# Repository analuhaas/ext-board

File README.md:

# External measurement board

As part of the CARROTS project, we develop a MMC prototype using the OwnTech Suite. WP1 develops the hardware prototype. WP2 and WP3 use this prototype to develop and test decentralized control and communication.

To do classic MMC closed-loop control, it is necessary to have external measurement boards to measure the DC voltage $u_{dc}$, DC current $i_{dc}$, phase voltage $v_{p}$, phase current $i_{p}$ and arm currents $i_{u,l}$. Also, the MMC start-up require a resistance + relay system on the DC/AC sides for current limitation. Figure 1 shows the necessary measurements outside of the modules and the position of the correspondent external measurement boards.

# Board structure

The external measurement board general structure is represented in Figure 2. It is composed of a power and a digital part separated by a galvanic isolation. The power part circuit is shown in Figure 3. It is composed of a power relay, 2 voltage measurements and 1 current measurement. The connectors A-B side is called "upstream" and connectors C-D side is called "downstream". The digital part is composed of a microcontroller (SPIN) that reads the measurements and sends to the controller and other modules via RS485 communication.

# KiCad schematic development

## Power circuit

The power part of the external measurement board is composed of a solid state relay that connects upstream side to downstream side, connectors that connects to the converter circuit and voltage/current sensors.

**Questions left for discussion:**

- **For now I have kept the backplane structure as used for the modules for compatibility, but we also evoked the possibility of using banana connectors.**
- **Added a 1 MΩ resistor R282 between PUPGND and PDOWNGND, so the two grounds are at the same voltage before the relay closes.**

## Voltage and current sensors

The measurement solution is the same used in the new module board. The voltage raw measurement is acquired using a voltage divisor. The current raw measurement is acquired by an IC current sensor.

Then, both raw measurements are amplified and sent to the digital part of the board using a galvanic isolated amplifier.

Finally, the voltage and current measurements are treated by an analog front-end that is able to change the sensor gain, offset and resolution according to the application.

**Questions left for discussion:**

- **Which value to use in R249 and R254?**

## SPIN

The SPIN is the microcontroller part of the board. The SPIN from OwnVerter solution is kept but some changes on the pinout were necessary:

- Adapt the pins to the measurements we implemented (Vup, Vdown, IAB)

- Add a command for the relay

## Communication

The RS485 communication is used to communicate the boards measurement with the controller/other modules of the converter. It can also receive commands to open/close the switch.

CAN and analog communications are also included in the schematic since they are a part of the base OwnTech solution.

The communication RJ45 terminals pins order are modified from latest board versions (TWIST V1.4.3 and OWNVERTER V1.1) to be correspondent to the pins used in the WP4 redesigned modules.

**Questions left for discussion:**

- **A adaptation to communicate with previous board versions is then necessary?**
- **Adaptation to communicate with 3 different buses**

## Auxiliary circuits supply

We adapted the auxiliary circuits supply feed generation of the microinverter project <https://github.com/owntech-foundation/micro-inverter>. The auxiliary circuits are fed by 5 VDGND, 5 VPUPGND and 5VPDOWNGND derived by the 12 VDGND input. The 12 VDGND input must be supplied by an external DC source.

The TPS7420 linear voltage regulator is used on the output of all +5V feeds to filter signal noises and keep the output on the target 5 V voltage.

**Questions left for discussion:**

- **Need to update the notes on consumption of the the supply circuits.**

## Datasheets referencing

There still some elements that have different datasheets reference (in PEBB too) compared to their LCSC number. Also there are some datasheets that are not specified:

**Datasheet referenced does not correspond to the LCSC part:**

**Datasheet not specified:**

- Connectors: U809 (PwrBlade 51722-10602-0020)

Passive elements, mounting holes (H1 to H6), solder jumpers (JP406, JP410, JP417) and the eurocard rails (N101) do not need a datasheet.

## BOM referencing

- No LCSC number: R249 and R254 (5.6 k 0805), and U809 (its value is also ~).

# KiCad Layout

## General structure

The board PCB has a structure divided in two parts, digital (upper) and power (lower), separated by a isolation area of 8 mm as defined by the IEC 60664 standard.

The board dimensions are reduced to 100mmx100mm compared to the usual 100mmx160mm of the OwnVerter/Twist boards.

The board keeps the same railtracks and mount holes for mechanical fixation as the OwnVerter/Twist boards. The 4 lower mount holes positions where adapted to position a safety bow around the board power part, avoiding user direct contact.

In the following sections, certain components positioning details are defined.

## Relay

The relay and its activation circuit on digital-side are shown in Figure 18. The relay is placed across the isolation area.

The activation circuit is placed in a certain distance from the relay to allow the placement of the security box.

##  Auxiliary supply for PUPGND/PDOWNGND referenced components

The CMT8830U power transformer is used to isolate the 5 VDGND to 5 VPUPGND/5 VPDOWNGND. The CMP6503S isolated power transformer driver is used to drive the transformer. In its datasheet, its recommended positioning with respect to the transformer is as shown in Figure 19.

The TPS7420 linear voltage regulator is used on the output of all +5V feeds to filter signal noises and keep the output on the target 5 V voltage. In its datasheet, its recommended positioning with respect to the input and output capacitors is as shown in Figure 20.

With the guidance of these datasheets indications the placement for the PDOWNGND referenced side was implemented as shown in Figure 21. The driver circuit is distanced from the transformer to allow the placement of the security box.

The placement for the PUPGND part is similar, but the buck circuit was moved to under the switch due to lack of space in the layout power part.

## Auxiliary supply for DGND referenced components

To pass from 12 VDGND to 5 VDGND voltage, the TPS562202 buck converter is used. The positioning of the commutation cell with respect to the other buck components are done as suggested in the datasheet as shown in Figure 23.

The TPS7420 linear voltage regulator is used on the output of all +5V feeds to filter signal noises and keep the output on the target 5 V voltage. In its datasheet, its recommended positioning with respect to the input and output capacitors is as shown in Figure 20.

The 5VDGND generation layout is shown in Figure 25.

## Voltage measurement circuit

The AMC1311x isolated amplifier is used to isolate the raw measurement of the power side from the digital measurement that is used by the MCU. In its datasheet, its recommended positioning with respect to the voltage divisor, input RC filter and decoupling capacitors is shown in Figure 26.

With the guidance of these datasheets indications the placement for both PUPGND/PDOWNGND referenced side was implemented as shown in Figure 27. The resistors where placed to avoid letting different potentials close to each other.

The analog-front end gets this digital output from the amplifier and adapts it according to user set gain, offset and resolution. The placement of the analog front-end for the 2 voltage measurements and current measurement was kept near the top part of the board as in the module boards developed by WP4, shown in Figure 28.

## Current measurement circuit

The ACS724 isolated current sensor is used to acquire the raw current measurement passing from A to B connectors of the board. There is no recommended layout position in its datasheet, so the components where placed as close as possible to the pins. To have a smaller current path, the current sensor was placed the closest as possible to the relay I+ pin and VDOWN connector.

Similarly to the voltage measurement, the AMC1311x isolated amplifier is used to isolate the raw measurement of the power side from the digital measurement that is used by the MCU. In its datasheet, its recommended positioning with respect to the voltage divisor, input RC filter and decoupling capacitors is shown in Figure 26.

With the guidance of these datasheets indications, the placement of the current measurement circuit was implemented as shown in Figure 29.

# Wiring development

## +12VDGND, +5VDGND, +5VPUPGND and +5VPDOWNGND feeding

The components feeding in the digital part was concentrated in the In2 layer. The widths of each one were estimated using the KiCad width calculator considering $\Delta T = 10 °C$ and H = 35 µm.

### +12VDGND width

To the left side, the +12VDGND input supplies the MOSFET that drives the relay and the realy. The relay consumption of the 12 V input is of 67 mA according to the microinverter project notes. Given this, we estimated:

| Current (A) | Conductor length (mm) | Calculated width (mm) |
|:-------------------------------:|:---------------------:|:---------------------:|
|0.067|72|0.0188|

To give a safety marge for the relay consumption and to use TWIST/SPIN usual values for feeding traces width, we used 0.25 mm width for the conductor feeding the relay + relay MOSFET.

To the right side, the +12VDGND input supplies all the other digital side components, since it feeds the +5VDGND and +5VDCLEARGND and the power side comonents, since the +5VDGND feeds the +5VPUPGND and +5VPDOWNGND. We make a list of its main components consumption in current:

| Component | Current (mA) |
|:----------|:-----------:|
| **+5VPUPGND loads** (fed through U802 + TR801 + U804) | |
| U205 AMC1311 isolated amplifier high-side supply (IDD1) | 9.7 |
| R38 transformer pre-load (5 V / 4.7 kΩ) | 1.1 |
| *Subtotal +5VPUPGND* | *10.8* |
| **+5VPDOWNGND loads** (fed through U803 + TR802 + U805) | |
| U207 AMC1311 isolated amplifier high-side supply (IDD1) | 9.7 |
| U211 AMC1311 isolated amplifier high-side supply (IDD1) | 9.7 |
| U801 ACS724 current sensor (ICC) | 15 |
| R58 transformer pre-load (5 V / 4.7 kΩ) | 1.1 |
| R280 + R281 divider on ACS724 output | 0.2 |
| *Subtotal +5VPDOWNGND* | *35.7* |
| **+5VDCLEANGND loads** (fed through U806) | |
| U205 AMC1311 isolated amplifier low-side supply (IDD2) | 8.1 |
| U207 AMC1311 isolated amplifier low-side supply (IDD2) | 8.1 |
| U211 AMC1311 isolated amplifier low-side supply (IDD2) | 8.1 |
| AFE801, AFE802, AFE807 analog front-ends (estimate, all three) | 100 |
| *Subtotal +5VDCLEANGND* | *124.3* |
| **+5VDGND loads** (fed by U14 buck) | |
| U401 SPIN (estimate) | 100 |
| U402 CA-IF1051S CAN transceiver | 80 |
| U405 CA-IF4850HS RS485 transceiver (driving 54 Ω) | 70 |
| U406 MCP6487 dual op-amp (2 × 0.72 mA) | 1.4 |
| R431 + R432 I2C pull-ups (both lines low) | 2.1 |
| U802 CMP6503S input (+5VPUPGND subtotal, η ≈ 52 %) | 22 |
| U803 CMP6503S input (+5VPDOWNGND subtotal, η ≈ 77 %) | 49.1 |
| U806 TPS7A2050 input (= +5VDCLEANGND subtotal) | 124.3 |
| ***Total +5VDGND*** | ***448.9*** |

The CMP6503S input currents are calculated as $I_{in} = I_{out} \cdot V_{out} / (\eta \cdot V_{in})$, with $V_{out} \approx 5.3$ V after the rectifier and $\eta$ read from the CMP6503S datasheet curves (Fig. 8.7 and 8.11, measured with the CMT6870N transformer). The linear voltage regulators TPS7A2050PDBVR input current is equal to their output current. The TPS562202 input current is calculated as $I_{12V} = I_{5V} \cdot 5.07 / (\eta \cdot 12)$, with $\eta \approx 93 \%$ and $I_{5V} = 448.9$ mA from the TPS562202 datasheet (Fig. 7-14, $V_{in}$ = 12 V, $V_{out}$ = 5 V).

This gives us a total current of 0.204 A for the right side branch.

We also could do a estimation of possible current consumption considering 3 W, which gives 3/12 = 0.25 A, which is very close to the value from the datasheets.

The current of 0.25 A is taken into account since it is the biggest. With this current, we estimated the width:

| Current (A) | Conductor length (mm) | Calculated width (mm) |
|:-------------------------------:|:---------------------:|:---------------------:|
|0.25|23|0.11|

To give a safety marge and to use TWIST/SPIN usual values for feeding traces width, we used 0.5 mm width for the conductor feeding the TPS562202 component.

### +5VDGND width

Since the +5VDCLEARGND consumption is directly connected to +5VDGND with a copper zone, we consider only 324.6 mA consumption to define the wires width.

| Current (A) | Conductor length (mm) | Calculated width (mm) |
|:-------------------------------:|:---------------------:|:---------------------:|
|0.324|19|0.16|

To give a safety marge and to use TWIST/SPIN usual values for feeding traces width, we used 0.5 mm width for the conductor feeding the branches RS485 transceiver + SPIN/CAN + Analog + CMP6503S + transformer D-PUP D-PDOWN.

### +5VPUPGND and +5VPDOWNGND width

As the division of load between the two +5VDGND branches are quite equilibrated, from this point ownwards, we consider 0.5 mm or 0.25 mm width are sufficient.

### +5VDCLEARGND width

The +5VDCLEARGND consumption is 124.3 mA, so we calculate the width.

| Current (A) | Conductor length (mm) | Calculated width (mm) |
|:-------------------------------:|:---------------------:|:---------------------:|
|0.125|137|0.0444|

To give a safety marge and to use TWIST/SPIN usual values for feeding traces width, we used 0.5 mm width for the conductor feeding of the +5VDCLEARGND branches.

The resulting feeding wired for the digital and power side components is given on Figures 30 and 31. The feeding on the digital side is on In2 layer and the feeding on the power side is on In1 layer.

## Power circuit

The power circuit composed by relay + current and voltage measurements (see Figure 4) needs to have its wiring compatible to the current passing by each branch.

### VDOWN to current sensor

Using a copper plane of 17 mm width (Y axis) and 10 mm length (X axis), we do a path between VDOWN terminal and the current sensor as in Figure 32.

### Current sensor to relay

Using a copper plane of 17 mm width (Y axis) and 22 mm length (X axis), we do a path between the current sensor and the relay as in Figure 33.

### Relay to VUP terminal

Using a copper plane of 17 mm width (Y axis) and 45 mm length (X axis), we do a path between the relay and the VUP terminal as in Figure 33.

### Voltage measurement voltage divider

The path to the voltage measurement voltage divider consumes some current from the main current path. Considering worst can scenario where VUP or VDOWN voltage peak is 800 V, the current demand is related to the voltage divider total impedance (see Figure 5).

Using that $R = 5 \cdot 0.33 = 1.65 M \Omega$, the current demand would be $I = \frac{800}{1.65\cdot 10^6}=0.485$ mA

Using the calculator again with this current and the lengths between the relay and the voltage dividers. Remark, we consider that the inner copper layer width is 17.5 µm.

| Current (mA) | Conductor length (mm) | Calculated width (um) |
|:-------------------------------:|:---------------------:|:---------------------:|
|0.485|72|41.9|
|0.485|32|41.9|

We use 0.5 mm width for safety margin. The resulting wiring for the power circuit is given on Figure 35.

## Signals

All other signals are wired in the front and bottom layers. The resulting wiring is shown in Figure 36.

## Used vias

According to JLCPCB, the minimum hole diameter of vias for the default configuration is 0.3 mm. The via diameter should be +0.15 mm than the hole size, so 0.45 mm.

We used the via size of 0.3 mm/0.45 mm for thermal dissipation of TPS562202. Other vias are of standard 0.4 mm/0.8 mm size proposed in KiCad.

## Layers copper thickness

According to JLCPCB, the default copper thickness for outer layers is 1 oz (= 35 µm) and for inner layers is 0.5 oz (=17.5 µm).

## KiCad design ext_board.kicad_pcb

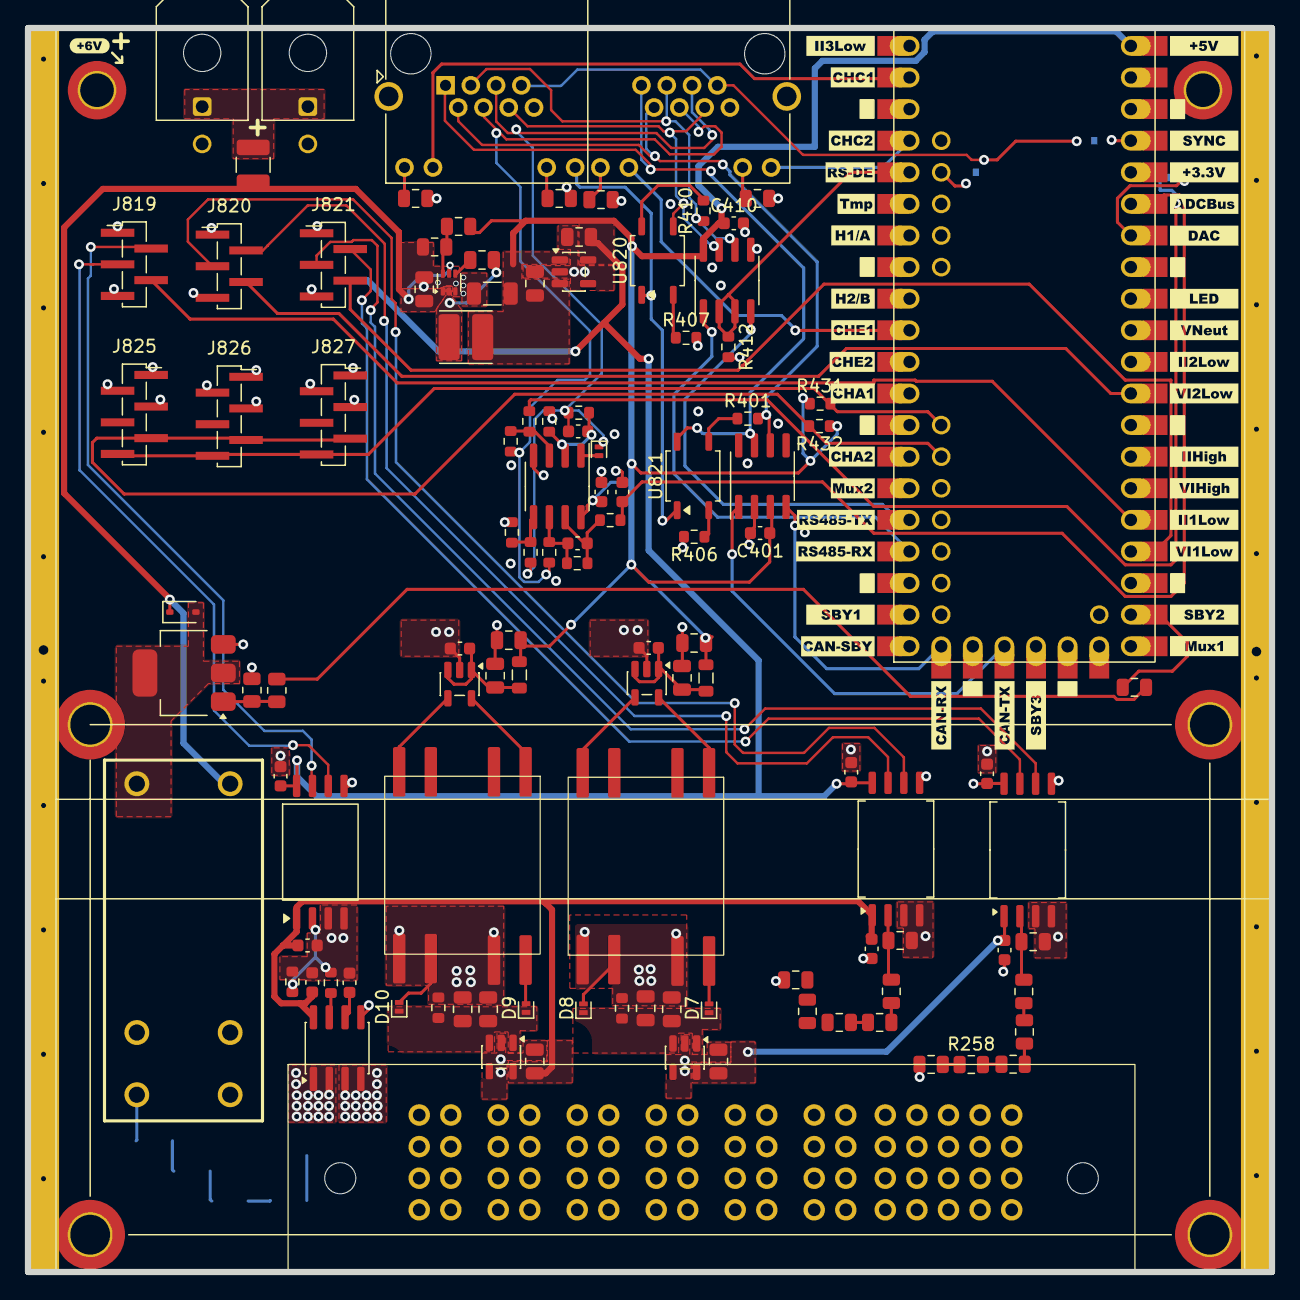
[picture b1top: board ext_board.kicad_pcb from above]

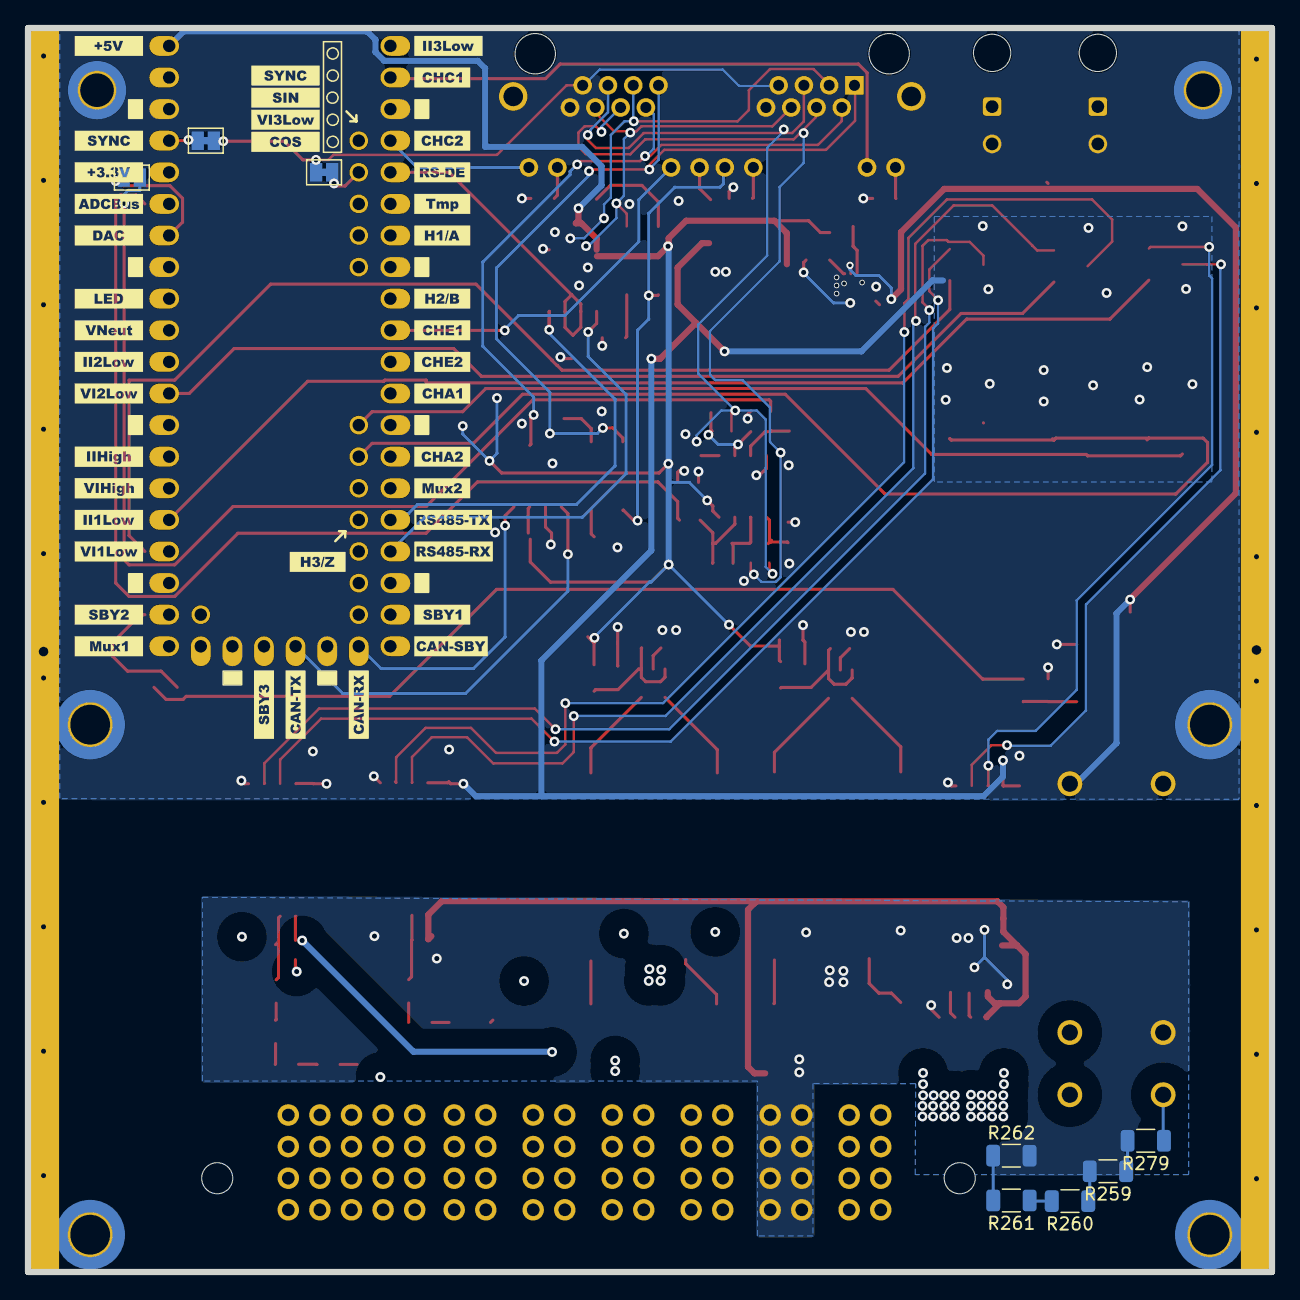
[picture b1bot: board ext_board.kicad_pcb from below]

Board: 4 copper layers, 100.0 x 100.0 mm, 202 parts (48 on the bottom side), 95 nets.

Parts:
C2, C3, C4, C5, C43, C44, C51: 10uF; C_0805_2012Metric
C41, C42, C205, C206, C211, C212, C233, C234, C401, C410, C413, C492: 100nF; C_0603_1608Metric
C45, C46, C47, C48, C49, C50: 1uF; C_0805_2012Metric
C52: 100nF; C_0805_2012Metric
C53: 47uF; C_1206_3216Metric
C411, C412: 20pF; C_0603_1608Metric
C470: 10nF; C_0603_1608Metric
C493: 1nF; C_0603_1608Metric
D6: 40V - BAT165E6327F; D_SOD-323
D7, D8, D9, D10: PMEG4010ESBYL; D_SOD-882
D403: BAS40DB; D_SOD-882
F402: SMD1210-035-16V; Fuse_1210_3225Metric
H1, H2: M2.5; MountingHole_2.7mm_M2.5_DIN965_Pad_TopBottom
H3, H4, H5, H6: M3x3.5; MountingHole_3.2mm_M3_DIN965_Pad_TopBottom
J405, J406: HC-MX3.0-2*1AW; Molex_Micro-Fit_3.0_43045-0200_2x01_P3.00mm_Horizontal
J813: RJ45_LED_Shielded_x2; RJ45_Amphenol_RJHSE538X-02
J819, J820, J821: PinSocket_1x05_P1.27mm_Vertical_SMD_Pin1Left
J825, J826, J827: PinSocket_1x06_P1.27mm_Vertical_SMD_Pin1Right
JP406, JP410, JP417: Jumper_2_Bridged; SolderJumper-2_P1.3mm_Bridged_Pad1.0x1.5mm
K801: HF140FF/012-2HSWTF; RELAY-TH_HF140FF-024-2HSWT
L2, L3: 10uH; L_0805_2012Metric
L5: 4.7uH - 80mR; L_Cenker_CKCS4020
N101: Eurocard rails; Guard_ring
Q12: ZXMN7A11GTA; SOT-223
R36: 47R; R_0805_2012Metric
R37, R57: 10k; R_0805_2012Metric
R38, R58, R412, R413, R414, R415, R416, R417, R418, R419, R428, R431, R432: 4.7k; R_0603_1608Metric
R55: 120R; R_0805_2012Metric
R56: 56k; R_0805_2012Metric
R249, R254: 5.6k; R_0805_2012Metric
R250, R251, R252, R255, R256, R257, R258, R269, R277, R278: 330k; R_0805_2012Metric
R259, R260, R261, R262, R279: 330k; R_1206_3216Metric
R280: 15k; R_0603_1608Metric
R281: 10k; R_0603_1608Metric
R401, R410, R470: 120R; R_0603_1608Metric
R402, R403, R404, R405: 330R; R_0805_2012Metric
R406, R407: 680R; R_0603_1608Metric
TR801, TR802: CMT8830U; CMT88F0U
U14: TPS562202; SOT-563
U205, U207, U211: AMC1311BDWVR; SOIC-8_7.5x5.85mm_P1.27mm
U401: OwnTech_SPIN; OwnTech_SPINTHT_1
U402: CA-IF1051S; SOIC-8_3.9x4.9mm_P1.27mm
U405: CA-IF4850HS; SOIC-8_3.9x4.9mm_P1.27mm
U406: MCP6487T-E/SN; SOIC-8_3.9x4.9mm_P1.27mm
U801: ACS724LLCTR-50AB-T-JSM; SOIC-8_3.9x4.9mm_P1.27mm
U802, U803: CMP6503S; SOT-23-5
U804, U805, U806: TPS7A20xxxDBV; SOT-23-5
U809: PwrBlade51722-106020
U820, U821: GAQY221S; SOP-4_3.8x4.1mm_P2.54mm
kibuzzard-68EE2A82: G***; kibuzzard-68EE2A82
kibuzzard-68EE3B36: G***; kibuzzard-68EE3B36
kibuzzard-68EE4C07: G***; kibuzzard-68EE4C07
kibuzzard-68EE24A5: G***; kibuzzard-68EE24A5
kibuzzard-68EE24AF: G***; kibuzzard-68EE24AF
kibuzzard-68EE24B5: G***; kibuzzard-68EE24B5
kibuzzard-68EE24BE: G***; kibuzzard-68EE24BE
kibuzzard-68EE24D4: G***; kibuzzard-68EE24D4
kibuzzard-68EE24E5: G***; kibuzzard-68EE24E5
kibuzzard-68EE24F3: G***; kibuzzard-68EE24F3
kibuzzard-68EE25AA: G***; kibuzzard-68EE25AA
kibuzzard-68EE25BE: G***; kibuzzard-68EE25BE
kibuzzard-68EE25CD: G***; kibuzzard-68EE25CD
kibuzzard-68EE43ED: G***; kibuzzard-68EE43ED
kibuzzard-68EE43F5: G***; kibuzzard-68EE43F5
kibuzzard-68EE44CF: G***; kibuzzard-68EE44CF
kibuzzard-68EE44DF: G***; kibuzzard-68EE44DF
kibuzzard-68EE44EF: G***; kibuzzard-68EE44EF
kibuzzard-68EE45B1: G***; kibuzzard-68EE45B1
kibuzzard-68EE45BE: G***; kibuzzard-68EE45BE
kibuzzard-68EE45CB: G***; kibuzzard-68EE45CB
kibuzzard-68EE45EE: G***; kibuzzard-68EE45EE
kibuzzard-68EE46AF: G***; kibuzzard-68EE46AF
kibuzzard-68EE46C1: G***; kibuzzard-68EE46C1
kibuzzard-68EE46D0: G***; kibuzzard-68EE46D0
kibuzzard-68EE46DF: G***; kibuzzard-68EE46DF
kibuzzard-68EE46EE: G***; kibuzzard-68EE46EE
kibuzzard-68EE46FA: G***; kibuzzard-68EE46FA
kibuzzard-68EE47A2: G***; kibuzzard-68EE47A2
kibuzzard-68EE47C7: G***; kibuzzard-68EE47C7
kibuzzard-68EE47E7: G***; kibuzzard-68EE47E7
kibuzzard-68EE71D6: G***; kibuzzard-68EE71D6
kibuzzard-68EE71F4: G***; kibuzzard-68EE71F4
kibuzzard-68EE71FA: G***; kibuzzard-68EE71FA
kibuzzard-68EE241F: G***; kibuzzard-68EE241F
kibuzzard-68EE244B: G***; kibuzzard-68EE244B
kibuzzard-68EE255F: G***; kibuzzard-68EE255F
kibuzzard-68EE260A: G***; kibuzzard-68EE260A
kibuzzard-68EE263D: G***; kibuzzard-68EE263D
kibuzzard-68EE264C: G***; kibuzzard-68EE264C
kibuzzard-68EE450D: G***; kibuzzard-68EE450D
kibuzzard-68EE470A: G***; kibuzzard-68EE470A
kibuzzard-68EE477F: G***; kibuzzard-68EE477F
kibuzzard-68EE721A: G***; kibuzzard-68EE721A
kibuzzard-68EE2327: G***; kibuzzard-68EE2327
kibuzzard-68EE2338: G***; kibuzzard-68EE2338
kibuzzard-68EE2344: G***; kibuzzard-68EE2344
kibuzzard-68EE2352: G***; kibuzzard-68EE2352
kibuzzard-68EE2407: G***; kibuzzard-68EE2407
kibuzzard-68EE2434: G***; kibuzzard-68EE2434
kibuzzard-68EE2472: G***; kibuzzard-68EE2472
kibuzzard-68EE2482: G***; kibuzzard-68EE2482
kibuzzard-68EE2491: G***; kibuzzard-68EE2491
kibuzzard-68EE2506: G***; kibuzzard-68EE2506
kibuzzard-68EE2514: G***; kibuzzard-68EE2514
kibuzzard-68EE2525: G***; kibuzzard-68EE2525
kibuzzard-68EE2547: G***; kibuzzard-68EE2547
kibuzzard-68EE2570: G***; kibuzzard-68EE2570
kibuzzard-68EE2583: G***; kibuzzard-68EE2583
kibuzzard-68EE2597: G***; kibuzzard-68EE2597
kibuzzard-68EE2618: G***; kibuzzard-68EE2618
kibuzzard-68EE2628: G***; kibuzzard-68EE2628
kibuzzard-68EE4414: G***; kibuzzard-68EE4414
kibuzzard-68EE4445: G***; kibuzzard-68EE4445
kibuzzard-68EE4488: G***; kibuzzard-68EE4488
kibuzzard-68EE4573: G***; kibuzzard-68EE4573
kibuzzard-68EE4580: G***; kibuzzard-68EE4580
kibuzzard-68EE4598: G***; kibuzzard-68EE4598
kibuzzard-68EE4753: G***; kibuzzard-68EE4753
kibuzzard-68EE4764: G***; kibuzzard-68EE4764
kibuzzard-68EE4773: G***; kibuzzard-68EE4773
kibuzzard-68EE4806: G***; kibuzzard-68EE4806
kibuzzard-68EE4815: G***; kibuzzard-68EE4815
kibuzzard-68EE4829: G***; kibuzzard-68EE4829
kibuzzard-68EE7214: G***; kibuzzard-68EE7214

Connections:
+5V_{DCLEANGND}: C50.1, C206.1, C212.1, C234.1, J819.1 (+5V), J820.1 (+5V), J821.1 (+5V), J825.11 (A2), J827.9 (A0), U205.8 (VDD2), U207.8 (VDD2), U211.8 (VDD2), U806.5 (OUT)
+5V_{DGND}: C2.1, C3.1, C49.1, C53.1, C401.1, C410.1, C413.1, L2.1, L3.1, L5.2, R56.1, R431.1, R432.1, U401.40 (+VIN), U402.3 (VCC), U405.8 (VCC), U406.8 (V+), U806.1 (IN), U806.3 (EN)
+5V_{PDOWNGND}: C47.1, C211.1, C233.1, C492.2, U207.1 (VDD1), U211.1 (VDD1), U801.8 (VCC), U805.5 (OUT)
+5V_{PUPGND}: C46.1, C205.1, U205.1 (VDD1), U804.5 (OUT)
+12V_{DGND}: C51.1, D6.1 (K), F402.2, K801.8, U14.1 (VIN), U14.5 (EN)
/Current sensor/I+: K801.5, R277.1, U801.1 (IP+), U801.2 (IP+)
/Current sensor/Iout_N: J819.3 (IN-), U211.6 (VOUTN)
/Current sensor/Iout_P: J819.2 (IN+), U211.7 (VOUTP)
/IAB_{MCU}: J819.4 (OUT), U401.25 (PC1)
/Isolated amplifier DOWN/vout_N: J820.3 (IN-), U207.6 (VOUTN)
/Isolated amplifier DOWN/vout_P: J820.2 (IN+), U207.7 (VOUTP)
/Isolated amplifier UP/vout_N: J821.3 (IN-), U205.6 (VOUTN)
/Isolated amplifier UP/vout_P: J821.2 (IN+), U205.7 (VOUTP)
/MCU/A: J813.3, J813.15, R410.1, U405.6 (A)
/MCU/ADC2_IN5: C470.1, R470.1, U401.35 (PC4)
/MCU/B: J813.6, J813.18, U405.7 (B), U820.3
/MCU/CAN_H: J813.1, J813.13, U402.7 (CANH), U821.4
/MCU/CAN_L: J813.2, J813.14, R401.2, U402.6 (CANL)
/MCU/DAC2: JP417.1 (A), U401.34 (PA6)
/MCU/FDCAN2_{RX}: U401.53 (PB5), U402.4 (RXD)
/MCU/FDCAN2_{TX}: U401.55 (PB6), U402.1 (TXD)
/MCU/HRTIM1_SCIN: J813.7, J813.19, JP406.2 (B), JP410.2 (B)
/MCU/Module_{Status}: J813.24, U401.4 (PB13)
/MCU/PB1: JP406.1 (A), U401.37 (PB1)
/MCU/PB2: JP410.1 (A), U401.42 (PB2)
/MCU/PC13: R55.1, U401.22 (PC13)
/MCU/Power_EN: J813.22, U401.10 (PC8)
/MCU/SHARE+: C412.2, D403.1 (K), J813.5, J813.17, R416.2, R419.2
/MCU/SHARE-: J813.4, J813.16, R417.2, R418.2
/MCU/TERM120: J813.12, U820.1, U821.1
/MCU/USART3_DE: R412.1, U401.5 (PB14), U405.2 (~RE), U405.3 (DE)
/MCU/USART3_RX: U401.17 (PC11), U405.1 (RO)
/MCU/USART3_TX: U401.16 (PC10), U405.4 (DI)
/MCU/USB_{STATUS}: J813.10, U401.2 (PB12)
/Relay: R36.1, R55.2
/SCL_{MCU}: J825.6 (SCL), J826.6 (SCL), J827.6 (SCL), R431.2, U401.46 (PA13)
/SDA_{MCU}: J825.7 (SDA), J826.7 (SDA), J827.7 (SDA), R432.2, U401.47 (PA14)
/VDOWN_{MCU}: J820.4 (OUT), U401.29 (PA0)
/VDOWN_{RAW}: R249.1, R252.2, U207.2 (VIN)
/VUP_{MCU}: J821.4 (OUT), U401.24 (PC0)
/VUP_{RAW}: R254.1, R255.2, U205.2 (VIN)
/V_{DOWN}: U801.3 (IP-), U801.4 (IP-), U809.1
/V_{UP}: K801.6, R278.1, U809.3
DGND: C2.2, C3.2, C4.2, C5.2, C41.2, C42.2, C49.2, C50.2, C51.2, C53.2, C206.2, C212.2, C234.2, C401.2, C410.2, C413.2, C470.2, J405.2, J406.2, J813.8, J813.20, J819.5 (GND), J820.5 (GND), J821.5 (GND), J825.9 (A0), J825.10 (A1), J826.9 (A0), J826.10 (A1), J826.11 (A2), J827.10 (A1), J827.11 (A2), Q12.3 (S), R37.2, R57.2, R402.1, R403.1, R404.1, R405.1, R406.2, R407.2, R412.2, R414.1, R428.1, U14.3 (GND), U205.5 (GND2), U207.5 (GND2), U211.5 (GND2), U401.3 (GND), U401.8 (GND), U401.13 (GND), U401.18 (GND), U401.23 (GND), U401.28 (GND), U401.33 (GND), U401.38 (GND), U401.54 (GND), U401.57 (GND), U402.2 (GND), U405.5 (GND), U406.4 (V-), U802.2 (GND), U803.2 (GND), U806.2 (GND)
Earth_Protective: H1.1 (1_1), H2.1 (1_1), H3.1 (1_1), H4.1 (1_1), H5.1 (1_1), H6.1 (1_1), J813.SH, N101.1 (PAD_1)
unnamed: C411.1, R415.1, R470.2, U406.7
unnamed: D6.2 (A), K801.1, Q12.2 (D), Q12.4 (D)
unnamed: D7.2 (A), TR801.8 (SB)
unnamed: C43.1, C45.1, D7.1 (K), D8.1 (K), R38.1, U804.1 (IN), U804.3 (EN)
unnamed: D8.2 (A), TR801.6 (SB)
unnamed: D9.2 (A), TR802.8 (SB)
unnamed: D10.2 (A), TR802.6 (SB)
unnamed: C44.1, C48.1, D9.1 (K), D10.1 (K), R58.1, U805.1 (IN), U805.3 (EN)
unnamed: D403.2 (A), U406.1
unnamed: F402.1, J405.1, J406.1
unnamed: J813.9, R403.2
unnamed: J813.11, R402.2
unnamed: J813.21, R405.2
unnamed: J813.23, R404.2
unnamed: JP417.2 (B), R413.1
unnamed: Q12.1 (G), R36.2, R37.1
unnamed: R250.1, R269.2
unnamed: R250.2, R251.1
unnamed: R251.2, R252.1
unnamed: R255.1, R256.2
unnamed: R256.1, R257.2
unnamed: R257.1, R258.2
unnamed: R258.1, R278.2
unnamed: R259.1, R279.2
unnamed: R259.2, R260.1
unnamed: R260.2, R261.1
unnamed: R261.2, R262.1
unnamed: R269.1, R277.2
unnamed: R401.1, U821.3
unnamed: R406.1, U821.2
unnamed: R407.1, U820.2
unnamed: R410.2, U820.4
unnamed: TR801.1 (AA), U802.5 (VB1)
unnamed: TR801.4 (AB), U802.4 (VB2)
unnamed: TR802.1 (AA), U803.5 (VB1)
unnamed: TR802.4 (AB), U803.4 (VB2)
unnamed: C52.2, L5.1, U14.2 (SW)
unnamed: C52.1, U14.4 (VBST)
unnamed: R56.2, R57.1, U14.6 (VFB)
unnamed: R280.2, R281.1, U211.2 (VIN)
unnamed: R413.2, R417.1, U406.3 (+)
unnamed: C412.1, R414.2, R416.1, U406.2 (-)
unnamed: R419.1, R428.2, U406.5 (+)
unnamed: C411.2, R415.2, R418.1, U406.6 (-)
unnamed: C493.2, U801.6 (FILTER)
unnamed: R280.1, U801.7 (VIOUT)
unnamed: C4.1, C41.1, L2.2, U802.1 (VDD), U802.3 (SEL)
unnamed: C5.1, C42.1, L3.2, U803.1 (VDD), U803.3 (SEL)
PDOWNGND: C44.2, C47.2, C48.2, C211.2, C233.2, C492.1, C493.1, K801.3, R58.2, R249.2, R262.2, R281.2, TR802.5 (SA), TR802.7 (SA), U207.3 (SHTDN), U207.4 (GND1), U211.3 (SHTDN), U211.4 (GND1), U801.5 (GND), U805.2 (GND), U809.2
PUPGND: C43.2, C45.2, C46.2, C205.2, K801.4, R38.2, R254.2, R279.1, TR801.5 (SA), TR801.7 (SA), U205.3 (SHTDN), U205.4 (GND1), U804.2 (GND), U809.4
